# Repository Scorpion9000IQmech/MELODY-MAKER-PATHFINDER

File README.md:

# MY MELODY PLAYER PATHFINDER
---
it has all the normal essentials of XIAO RP2040 the 3 leds resistors and the keyswitches, the lights light up when the keys are pressed
however my design specifically focuses on the added buzzers, as a sequence of buttons is pressed, if it is a random sequence it will reflash the sequence of lights and make a TUNN sound, otherwise if its one of the passwords put in the code, it will play the corresponding melody, the melody could be played in a manner of approaches like the by melodyonallbuzzers function which makes all 3 play the melody, or the other ones that play it on only one buzzer, or the chords as well
this has a great potential if the time is taken to properly write down the notes of a song and its durations

I wanted to simply add buzzers at first but I thought of making some sort of music and stumbled upon the idea to make it so that it plays on its own if a sequence is entered

## IMAGE
---
### schematic and pcb

### case

### 3d view with componets

as shown on the pcb and the case, the board will be screwed in by 3mm diameter screws to secure it and be powered simply by the xiaorp4020 usb c cable

### I WILL BE PAYING FOR IT MYSELF
## BOM
---
| Parts | COST | LINK |
|-------|------|------|
| KEYSWITCH 10 peice | 7 USD | [Daraz](https://www.daraz.pk/products/mechanical-keyboard-switches-3-pin-rgb-hot-swappable-blue-red-brown-black-silent-tactile-switches-for-gaming-keyboard-70-million-clicks-durability-pc-gaming-keyboard-accessories-diy-keyboard-switches-set-i936558752-s3994103046.html) |
| Buzzers 10 peice | 1.58 USD | [AliExpress](https://ar.aliexpress.com/item/1005008165091345.html?spm=a2g0o.productlist.main.8.3c86xKOixKOitP&aem_p4p_detail=202604270416102094164706196300001174606&algo_pvid=e2f0ab90-6a1b-48cf-8a82-a7af61c8c830&algo_exp_id=e2f0ab90-6a1b-48cf-8a82-a7af61c8c830-7&pdp_ext_f=%7B"order"%3A"139"%2C"spu_best_type"%3A"price"%2C"eval"%3A"1"%2C"fromPage"%3A"search"%7D&pdp_npi=6%40dis%21USD%211.58%211.58%21%21%2110.75%2110.75%21%402140ec5d17772885701743231ef38d%2112000044055302230%21sea%21OM%216453760668%21X%211%210%21n_tag%3A-29911%3Bd%3A4b15dde3%3Bm03_new_user%3A-29895&curPageLogUid=FBDDN1ZaPHbf&utparam-url=scene%3Asearch%7Cquery_from%3A%7Cx_object_id%3A1005008165091345%7C_p_origin_prod%3A&search_p4p_id=202604270416102094164706196300001174606_2) |
| XIAO RP2040 | 6.31 USD | [AliExpress](https://ar.aliexpress.com/item/1005006593701624.html?spm=a2g0o.productlist.main.1.594e72a0k3wotb&algo_pvid=3994ba39-1c0d-4fbb-9548-68c0d8941582&algo_exp_id=3994ba39-1c0d-4fbb-9548-68c0d8941582-0&pdp_ext_f=%7B"order"%3A"447"%2C"eval"%3A"1"%2C"fromPage"%3A"search"%7D&pdp_npi=6%40dis%21USD%216.31%214.67%21%21%216.31%214.67%21%402140ec5d17772896468825754ef38f%2112000039072595754%21sea%21OM%216453760668%21X%211%210%21n_tag%3A-29911%3Bd%3A4b15dde3%3Bm03_new_user%3A-29895&curPageLogUid=k188lO9MGhtl&utparam-url=scene%3Asearch%7Cquery_from%3A%7Cx_object_id%3A1005006593701624%7C_p_origin_prod%3A) |
| LED 3 | --- | [AliExpress](https://ar.aliexpress.com/item/1005003144912658.html?spm=a2g0o.productlist.main.9.183212b2Q72sXj&algo_pvid=4e984bab-bf54-402b-a302-27637ba4f4f8&algo_exp_id=4e984bab-bf54-402b-a302-27637ba4f4f8-8&pdp_ext_f=%7B"order"%3A"1868"%2C"eval"%3A"1"%2C"fromPage"%3A"search"%7D&pdp_npi=6%40dis%21USD%2110.58%2110.58%21%21%2110.58%2110.58%21%402101364d17813370687882500eeddd%2112000024337656011%21sea%21OM%216453760668%21X%211%210%21n_tag%3A-29913%3Bd%3A74d2ffa1%3Bm03_new_user%3A-29895&curPageLogUid=bI9B1ShIDbtv&utparam-url=scene%3Asearch%7Cquery_from%3A%7Cx_object_id%3A1005003144912658%7C_p_origin_prod%3A) |
| Resistors 3 |---| [AliExpress](https://ar.aliexpress.com/item/1005011772534173.html?spm=a2g0o.productlist.main.1.2cd76c69ceROit&algo_pvid=387fe3d2-e112-40e6-b7d9-6ca5e3669256&algo_exp_id=387fe3d2-e112-40e6-b7d9-6ca5e3669256-0&pdp_ext_f=%7B"order"%3A"4292"%2C"spu_best_type"%3A"price"%2C"eval"%3A"1"%2C"fromPage"%3A"search"%7D&pdp_npi=6%40dis%21USD%2113.55%2113.55%21%21%2191.22%2191.22%21%402102f22c17813371416123830eeefa%2112000056500803485%21sea%21OM%216453760668%21X%211%210%21n_tag%3A-29913%3Bd%3A74d2ffa1%3Bm03_new_user%3A-29895&curPageLogUid=YmBREZctchqf&utparam-url=scene%3Asearch%7Cquery_from%3A%7Cx_object_id%3A10050117) |

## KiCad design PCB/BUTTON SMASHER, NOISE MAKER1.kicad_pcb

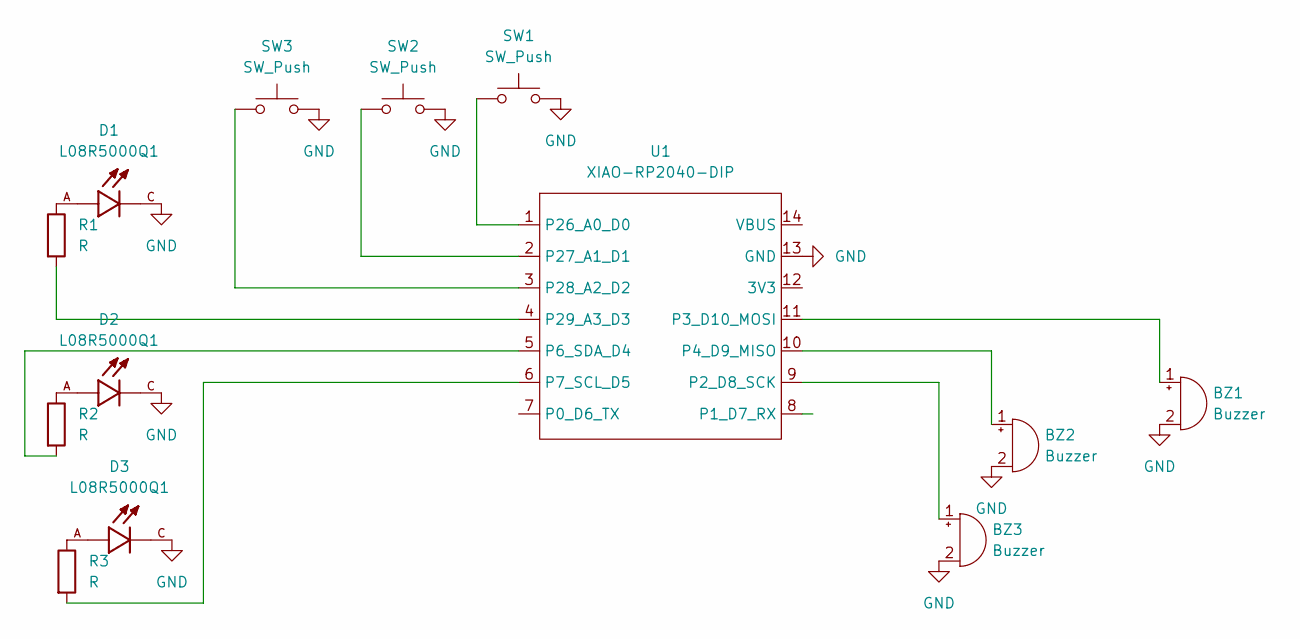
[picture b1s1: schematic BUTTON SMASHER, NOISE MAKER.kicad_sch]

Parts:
BZ1, BZ2, BZ3: Buzzer; Buzzer_12x9.5RM7.6
D1, D2, D3: L08R5000Q1; LEDRD254W57D500H1070; PARTREV NA
R1, R2, R3: R; R_Axial_DIN0204_L3.6mm_D1.6mm_P5.08mm_Horizontal
SW1, SW2, SW3: SW_Push; SW_Cherry_MX_1.00u_PCB
U1: XIAO-RP2040-DIP

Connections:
GND: BZ1.2 (-), BZ2.2 (-), BZ3.2 (-), D1.C, D2.C, D3.C, SW1.2, SW2.2, SW3.2, U1.13 (GND)
unnamed: BZ1.1 (+), U1.11 (P3_D10_MOSI)
unnamed: BZ2.1 (+), U1.10 (P4_D9_MISO)
unnamed: BZ3.1 (+), U1.9 (P2_D8_SCK)
unnamed: D1.A, R1.1
unnamed: D2.A, R2.1
unnamed: D3.A, R3.1
unnamed: R2.2, U1.5 (P6_SDA_D4)
unnamed: R3.2, U1.6 (P7_SCL_D5)
unnamed: SW1.1, U1.1 (P26_A0_D0)
unnamed: SW2.1, U1.2 (P27_A1_D1)
unnamed: SW3.1, U1.3 (P28_A2_D2)
unnamed: R1.2, U1.4 (P29_A3_D3)

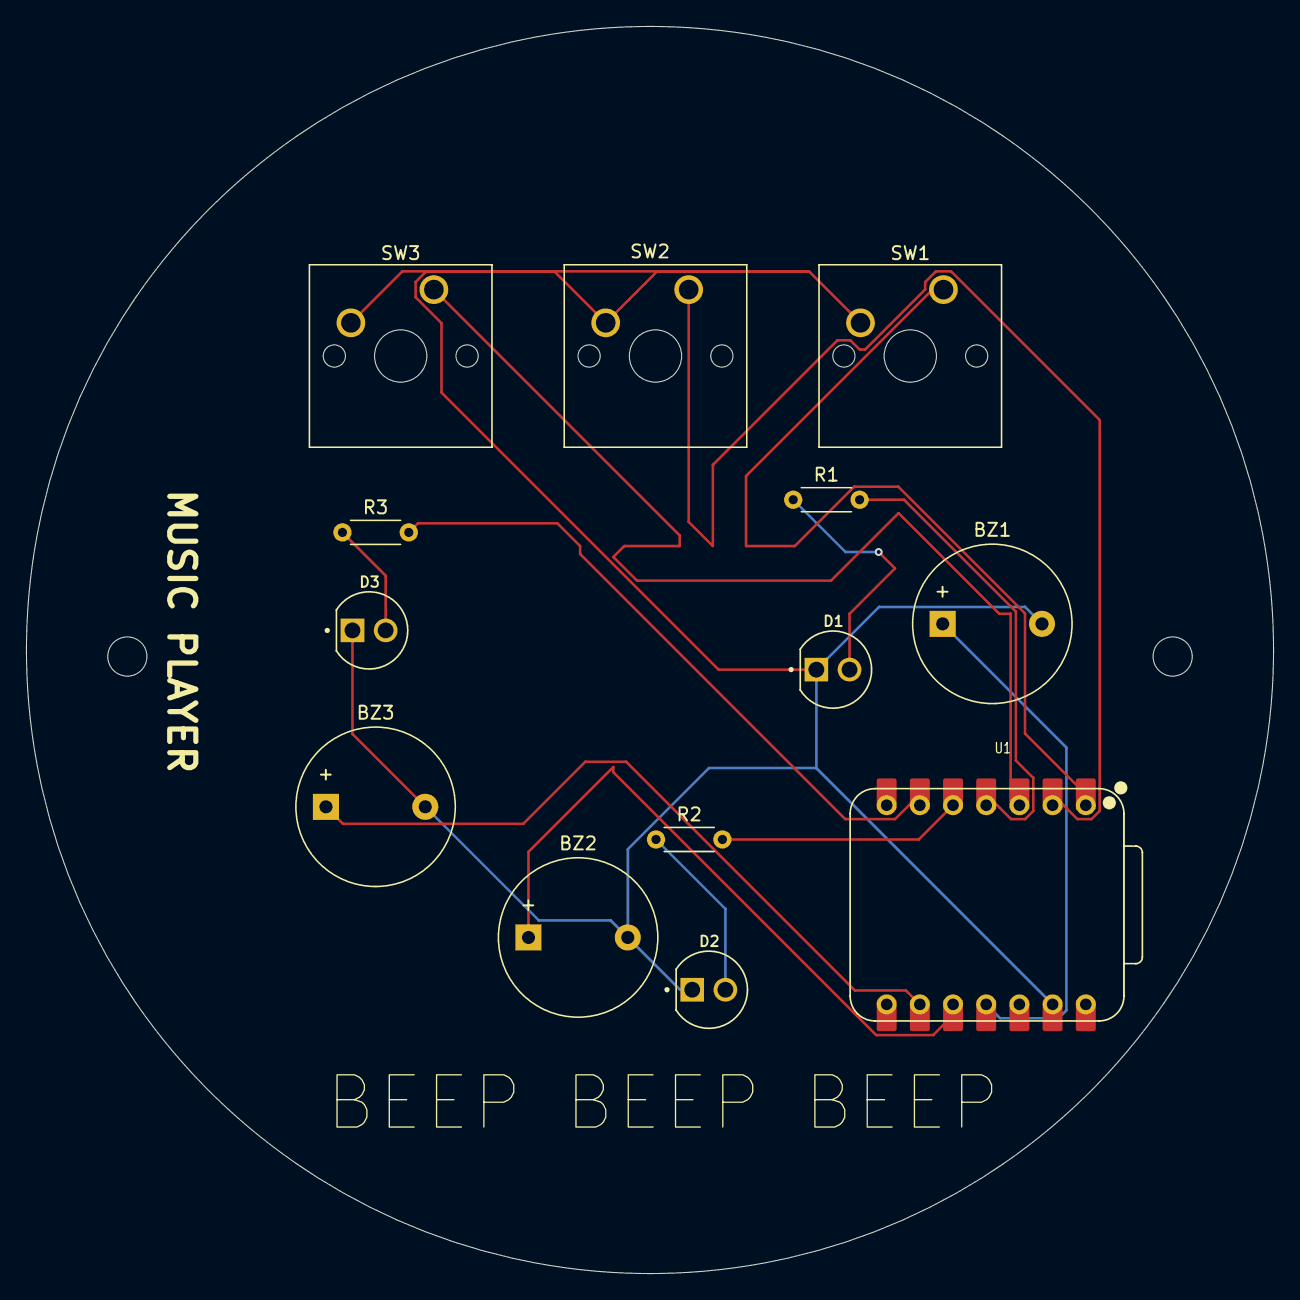
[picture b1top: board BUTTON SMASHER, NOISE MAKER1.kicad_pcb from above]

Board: 2 copper layers, 95.4 x 95.4 mm, 13 parts (0 on the bottom side), 13 nets.

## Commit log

2026-04-27 Rename BUTTON SMASHER, NOISE MAKER.kicad_sch to PCB/BUTTON SMASHER, NOISE MAKER.kicad_sch
2026-04-27 Rename BUTTON SMASHER, NOISE MAKER1.kicad_pcb to PCB/BUTTON SMASHER, NOISE MAKER1.kicad_pcb
2026-04-27 Rename BUTTON SMASHER, NOISE MAKER1.kicad_pro to PCB/BUTTON SMASHER, NOISE MAKER1.kicad_pro
2026-04-27 Create empty
2026-04-27 Update and rename BOM.csv to empty
